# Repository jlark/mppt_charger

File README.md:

# mppt_charger
small mppt solar charger with built in boost converter

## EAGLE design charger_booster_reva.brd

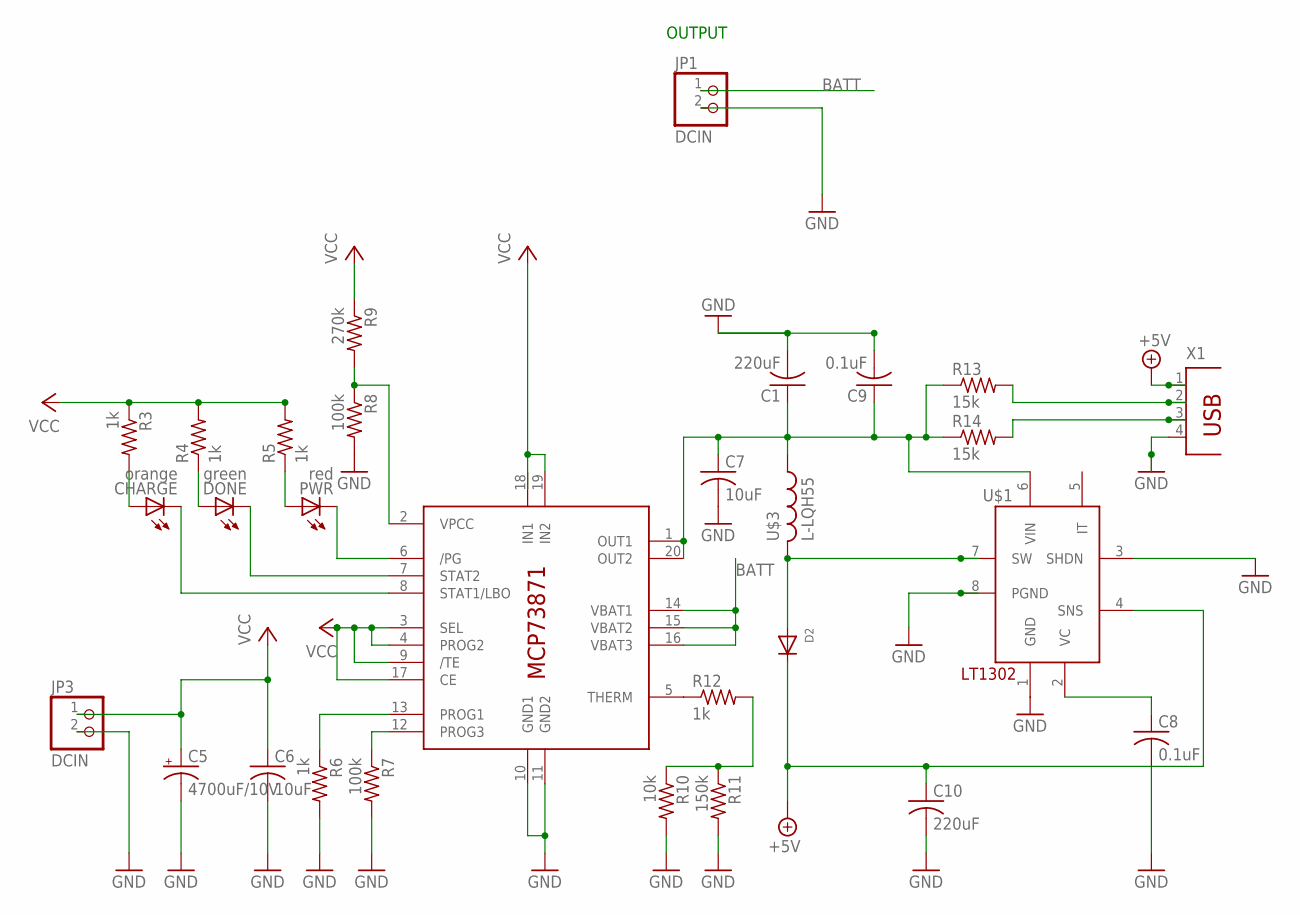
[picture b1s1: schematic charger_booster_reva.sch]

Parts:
C1, C10: 220uF; C0805K; MPN 12063D106KAT2A
C5: 4700uF/10V; E5-13
C6, C7: 10uF; C0805K; MPN 12063D106KAT2A
C8: 0.1uF; C0805K; MPN 12063D106KAT2A
C9: 0.1uF; C050-024X044; MPN 0402ZD104KAT2A
CHARGE: orange; CHIPLED_0805
D2: DIODESOD-523; SOD-523
DONE: green; CHIPLED_0805; MPN 150080GS75000
IC1: MCP73871; QFN20; MPN MCP73871-2CAI/ML
JP1, JP3: DCIN; 1X02
PWR: red; CHIPLED_0805; MPN 150080RS75000
R3, R4, R5, R6, R12: 1k; R0805; MPN MCF 0.25W 1K
R7, R8: 100k; R0805; MPN MCF 0.25W 100K
R9: 270k; R0805; MPN 08055A270KAT2A
R10: 10k; R0805; MPN MCHP05W4F1002T5E
R11: 150k; R0805; MPN MCHP05W4F1503T5E
R13, R14: 15k; R0805
U$1: LT1302; DIL08; MPN LT1302CN8-5#PBF
U$3: L-LQH55; LQH55
X1: PN87520

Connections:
+5V: C10.1, D2.K (C), U$1.4 (SNS), X1.1
BATT: IC1.14 (VBAT1), IC1.15 (VBAT2), IC1.16 (VBAT3), JP1.1
GND: C1.2, C5.-, C6.2, C7.2, C8.2, C9.2, C10.2, IC1.10 (GND1), IC1.11 (GND2), JP1.2, JP3.2, R6.2, R7.2, R8.2, R10.2, R11.2, U$1.1 (GND), U$1.3 (SHDN), U$1.8 (PGND), X1.4
unnamed: IC1.6 (/PG), PWR.C
unnamed: R14.2, X1.3
unnamed: R13.2, X1.2
unnamed: C8.1, U$1.2 (VC)
unnamed: D2.A, U$1.7 (SW), U$3.2
unnamed: CHARGE.A, R3.2
unnamed: IC1.13 (PROG1), R6.1
unnamed: CHARGE.C, IC1.8 (STAT1/LBO)
unnamed: DONE.C, IC1.7 (STAT2)
unnamed: IC1.12 (PROG3), R7.1
unnamed: DONE.A, R4.1
unnamed: PWR.A, R5.1
unnamed: IC1.5 (THERM), R12.1
unnamed: IC1.2 (VPCC), R8.1, R9.2
unnamed: R10.1, R11.1, R12.2
OUT: C1.1, C7.1, C9.1, IC1.1 (OUT1), IC1.20 (OUT2), R13.1, R14.1, U$1.6 (VIN), U$3.1
VCC: C5.+, C6.1, IC1.3 (SEL), IC1.4 (PROG2), IC1.9 (/TE), IC1.17 (CE), IC1.19 (IN2), JP3.1, R3.1, R4.2, R5.2, R9.1

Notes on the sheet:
OUTPUT

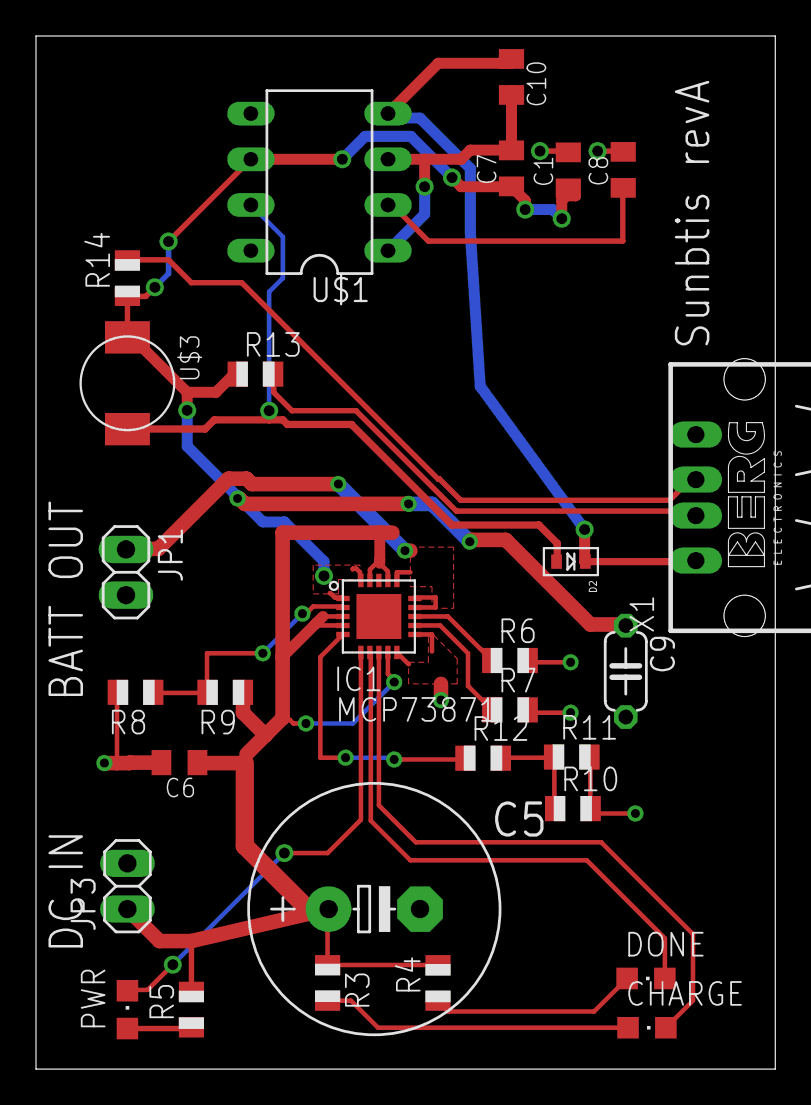
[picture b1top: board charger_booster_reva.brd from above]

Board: 2 copper layers, 41.1 x 57.4 mm, 29 parts (0 on the bottom side), 20 nets.

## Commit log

2015-07-13 adding source files
